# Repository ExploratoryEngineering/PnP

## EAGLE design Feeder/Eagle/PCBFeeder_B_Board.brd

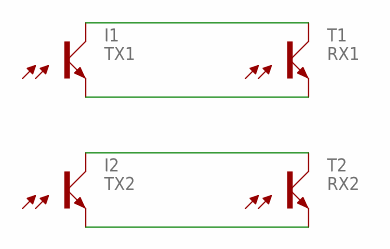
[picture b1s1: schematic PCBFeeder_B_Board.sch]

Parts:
I1: TX1; DIODE_BREAKOUT
I2: TX2; DIODE_BREAKOUT
T1: RX1; VEMT2020_PHOTOTRANSISTOR
T2: RX2; VEMT2020_PHOTOTRANSISTOR

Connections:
unnamed: I1.A, T1.A
unnamed: I1.C, T1.C
unnamed: I2.A, T2.A
unnamed: I2.C, T2.C

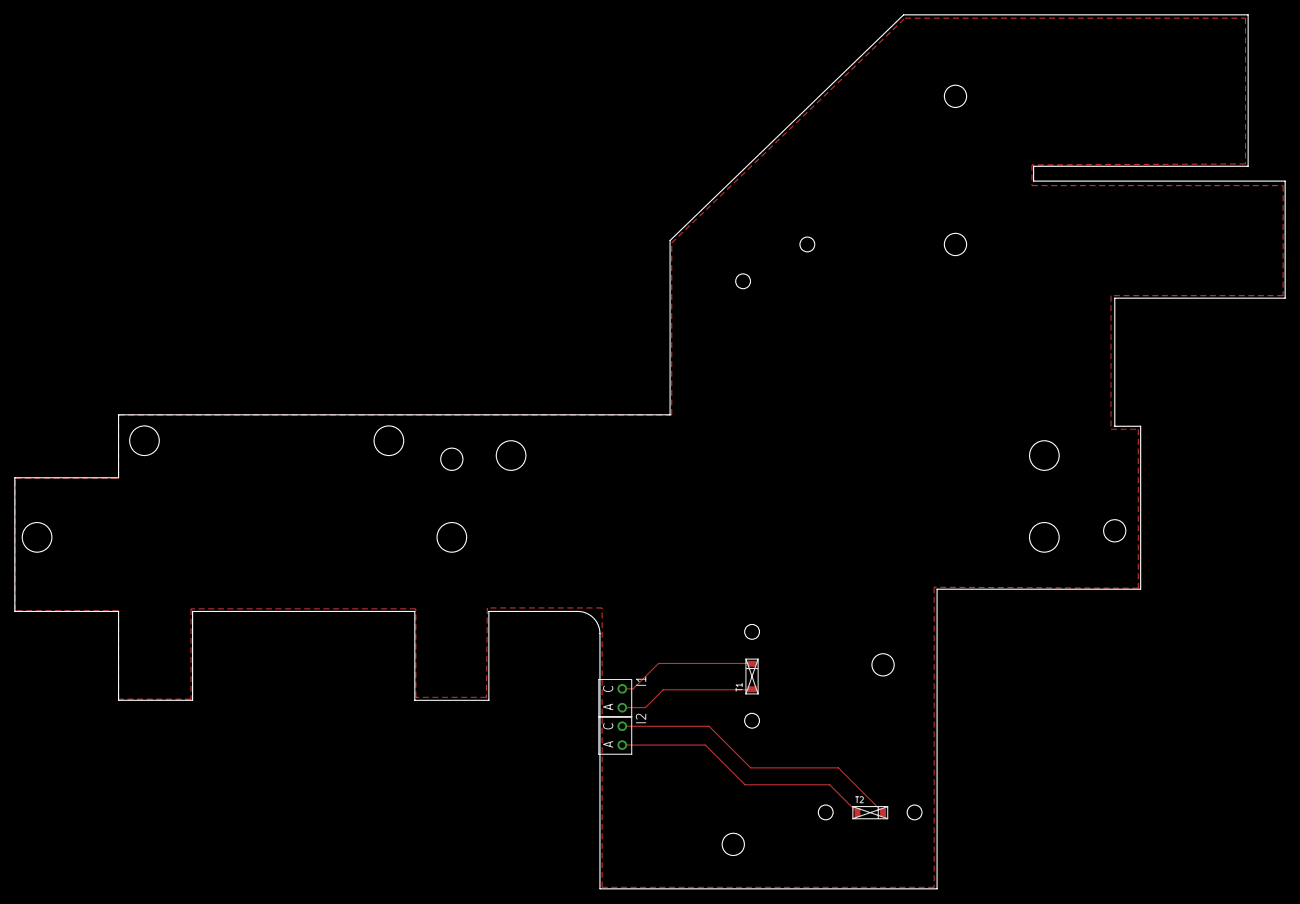
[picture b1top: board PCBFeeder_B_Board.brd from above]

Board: 2 copper layers, 171.5 x 118.0 mm, 4 parts (0 on the bottom side), 4 nets.

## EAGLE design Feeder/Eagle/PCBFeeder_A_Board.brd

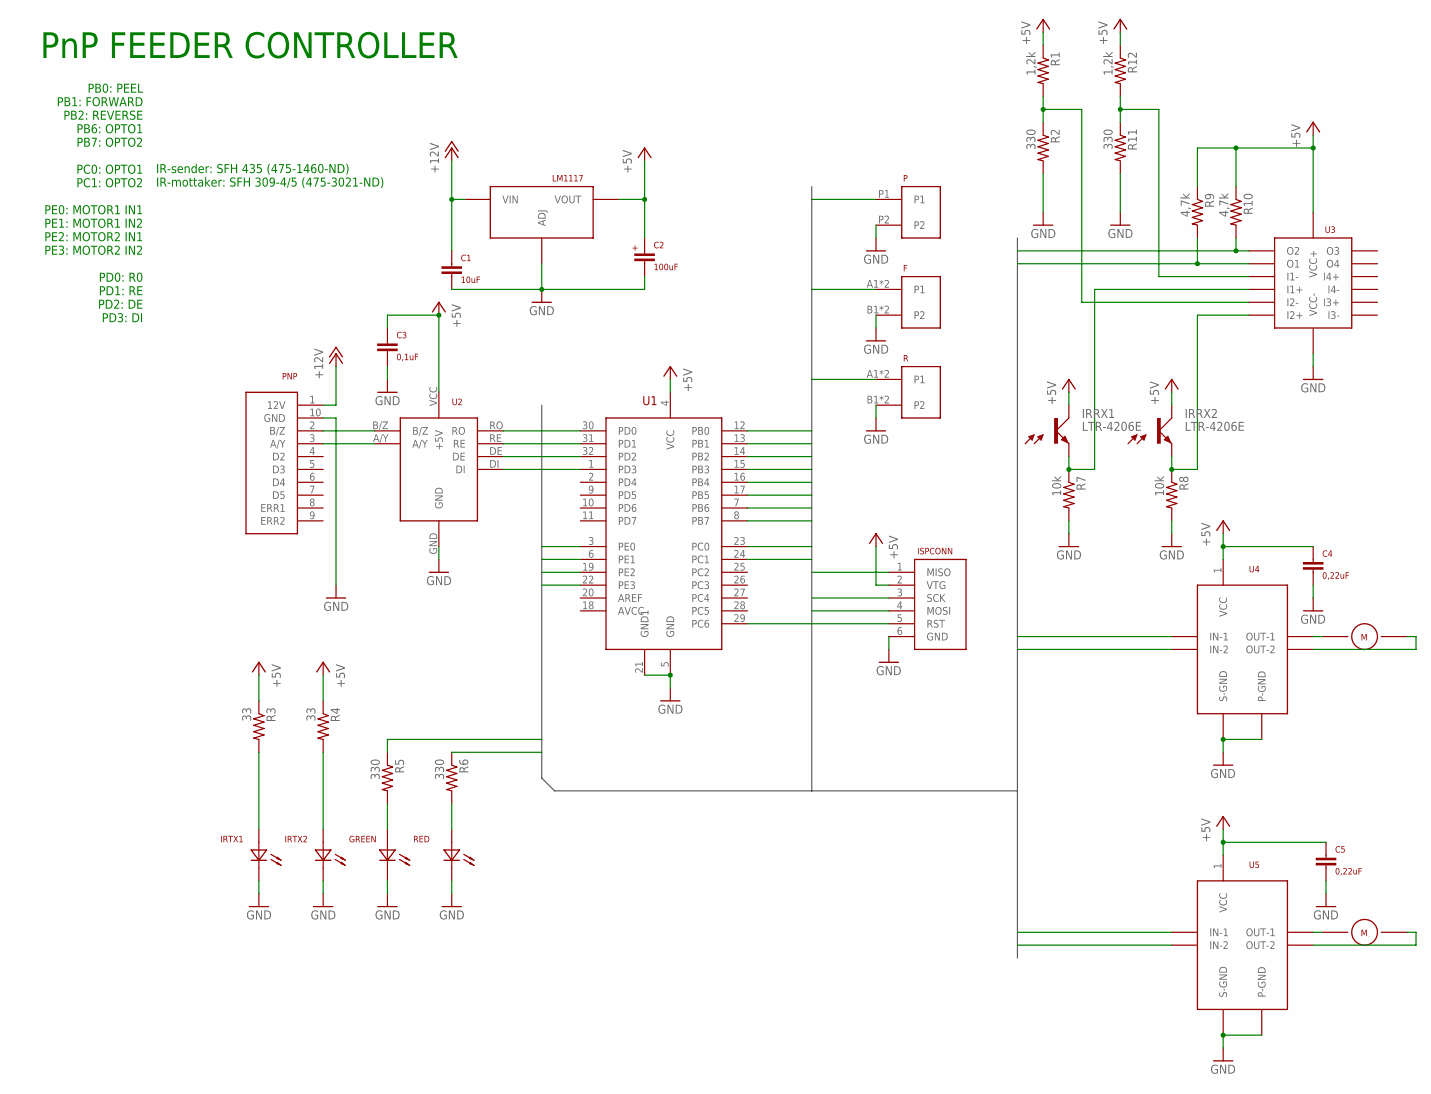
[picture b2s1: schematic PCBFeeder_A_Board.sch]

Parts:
C1: 10uF; 0805
C2: 100uF; ALUMINUM_WURTH_100UF_865080243007
C3: 0,1uF; 0805
C4, C5: 0,22uF; 0805
F: TERMINAL_2PSIDE_SWITCH; SIDE-PUSH-SWITCH
GREEN: LED; LED_859_KTST_S220KSKT
IRRX1, IRRX2: LTR-4206E; DIODE_BREAKOUT
IRTX1, IRTX2: IR204C_IR_EMITTER; IR_EMITTER_475-3009-1-ND
ISPCONN: ISP_PROG_HEADER; IDC_HEADER_6P
LM1117: LM1117; SOT-223
M1, M2: MOTOR254; SOLDER_CONNECTOR_2P_254
P: TERMINAL_2P254; SOLDER_CONNECTOR_2P_254
PNP: FEEDER_HEADER; IDC_HEADER_VERTICAL_10P
R: TERMINAL_2PSIDE_SWITCH; SIDE-PUSH-SWITCH
R1, R12: 1,2k; 0805
R2, R5, R6, R11: 330; 0805
R3, R4: 33; 0805
R7, R8: 10k; 0805
R9, R10: 4,7k; 0805
RED: LED; LED_859_KTST_S220KSKT
U1: MEGA168-AI; TQFP32-08
U2: ISL81487; ISL81487_RS485_TRANSCIEVER
U3: LM339; TSSOP14
U4, U5: LB1930MC-AH-MOTOR-DRIVER; SOIC-10

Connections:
+5V: C2.+, C3.1, C4.1, C5.1, IRRX1.A, IRRX2.A, ISPCONN.2 (VTG), LM1117.VOUT$1 (VOUT), R1.1, R3.1, R4.1, R9.1, R10.1, R12.1, U1.4 (VCC), U2.VCC (+5V), U3.P3 (VCC+), U4.1 (VCC), U5.1 (VCC)
+12V: C1.1, LM1117.VIN, PNP.1 (12V)
DE: U1.32 (PD2), U2.DE
DI: U1.1 (PD3), U2.DI
FORWARD: F.A1 (P1), F.A2 (P1), U1.13 (PB1)
GND: C1.2, C2.-, C3.2, C4.2, C5.2, F.B1 (P2), F.B2 (P2), GREEN.C, IRTX1.C, IRTX2.C, ISPCONN.6 (GND), LM1117.GND (ADJ), P.P2, PNP.10 (GND), R.B1 (P2), R.B2 (P2), R2.2, R7.2, R8.2, R11.2, RED.C, U1.5 (GND), U1.21 (GND1), U2.GND, U3.P12 (VCC-), U4.5 (S-GND), U4.6 (P-GND), U5.5 (S-GND), U5.6 (P-GND)
LED_G: R5.1, U1.24 (PC1)
LED_R: R6.1, U1.23 (PC0)
M1_IN1: U1.3 (PE0), U4.3 (IN-1)
M1_IN2: U1.6 (PE1), U4.4 (IN-2)
M2_IN1: U1.19 (PE2), U5.3 (IN-1)
M2_IN2: U1.22 (PE3), U5.4 (IN-2)
MISO: ISPCONN.1 (MISO), U1.16 (PB4)
MOSI: ISPCONN.4 (MOSI), U1.15 (PB3)
unnamed: PNP.2 (B/Z), U2.B/Z
unnamed: PNP.3 (A/Y), U2.A/Y
unnamed: IRRX1.C, R7.1, U3.P5 (I1+)
unnamed: IRRX2.C, R8.1, U3.P7 (I2+)
unnamed: R1.2, R2.1, U3.P6 (I2-)
unnamed: R11.1, R12.2, U3.P4 (I1-)
unnamed: M1.P1 (A), U4.9 (OUT-1)
unnamed: M1.P2 (B), U4.7 (OUT-2)
unnamed: M2.P1 (A), U5.9 (OUT-1)
unnamed: M2.P2 (B), U5.7 (OUT-2)
unnamed: IRTX1.A, R3.2
unnamed: IRTX2.A, R4.2
unnamed: GREEN.A, R5.2
unnamed: R6.2, RED.A
OPTO1: R9.2, U1.7 (PB6), U3.P2 (O1)
OPTO2: R10.2, U1.8 (PB7), U3.P1 (O2)
PEEL: P.P1, U1.12 (PB0)
RE: U1.31 (PD1), U2.RE
REVERSE: R.A1 (P1), R.A2 (P1), U1.14 (PB2)
RO: U1.30 (PD0), U2.RO
RST: ISPCONN.5 (RST), U1.29 (PC6)
SCK: ISPCONN.3 (SCK), U1.17 (PB5)

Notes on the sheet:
PB0: PEEL PB1: FORWARD PB2: REVERSE PB6: OPTO1 PB7: OPTO2 PC0: OPTO1 PC1: OPTO2 PE0: MOTOR1 IN1 PE1: MOTOR1 IN2 PE2: MOTOR2 IN1 PE3: MOTOR2 IN2 PD0: R0 PD1: RE PD2: DE PD3: DI
PnP FEEDER CONTROLLER
IR-sender: SFH 435 (475-1460-ND) IR-mottaker: SFH 309-4/5 (475-3021-ND)

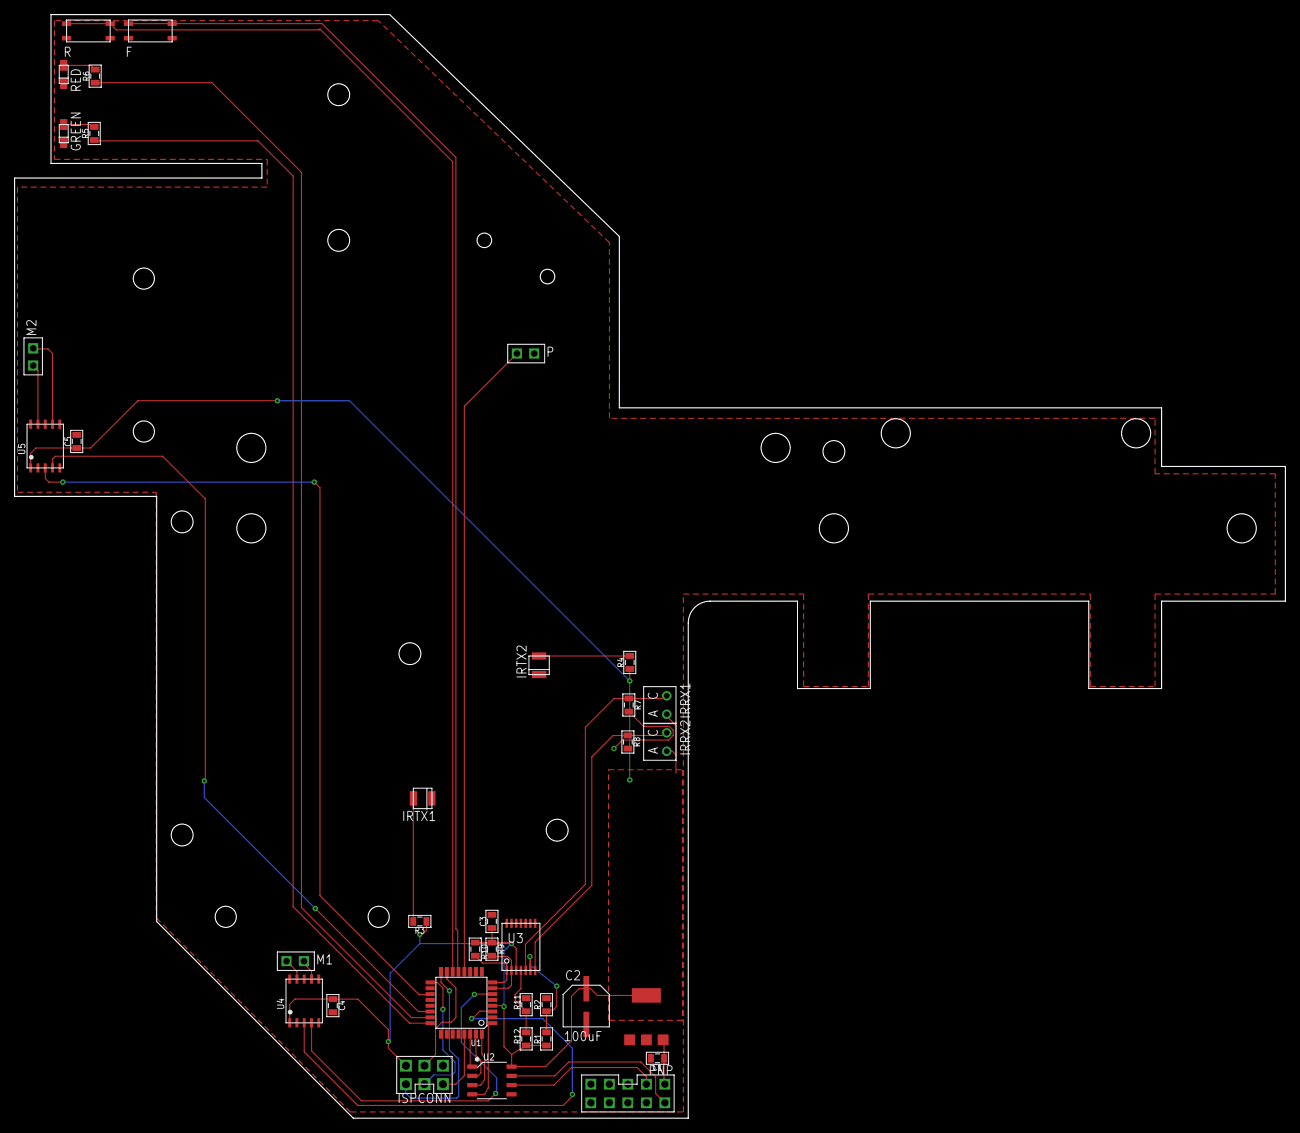
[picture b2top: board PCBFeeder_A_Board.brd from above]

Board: 2 copper layers, 174.5 x 151.5 mm, 36 parts (0 on the bottom side), 36 nets.

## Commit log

2018-03-12 Initial commit
    Added Feeder design
